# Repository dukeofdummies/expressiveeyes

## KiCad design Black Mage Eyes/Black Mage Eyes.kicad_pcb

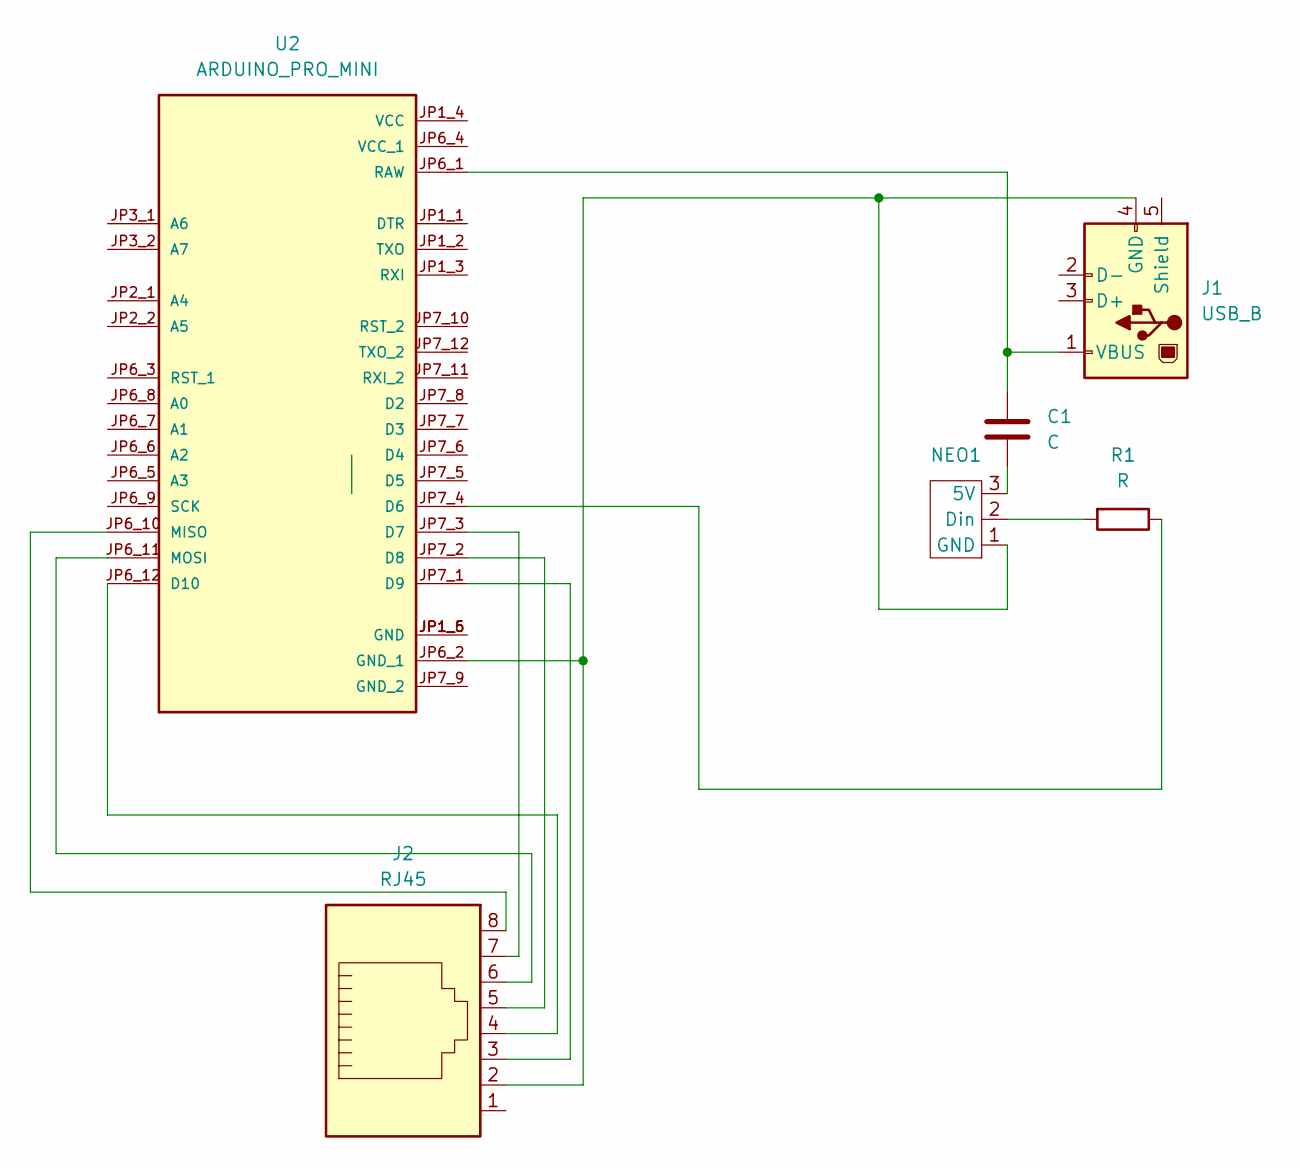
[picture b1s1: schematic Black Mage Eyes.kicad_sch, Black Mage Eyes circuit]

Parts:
C1: C; C_Radial_D8.0mm_H7.0mm_P3.50mm
J1: USB_B; USB_B_Amphenol_MUSB-D511_Vertical_Rugged
J2: RJ45; RJ45_Amphenol_54602-x08_Horizontal
NEO1: PinHeader_1x03_P2.00mm_Vertical
R1: R; R_Axial_DIN0207_L6.3mm_D2.5mm_P7.62mm_Horizontal
U2: ARDUINO_PRO_MINI; MODULE_ARDUINO_PRO_MINI; PARTREV N/A

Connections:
unnamed: J1.4 (GND), J2.2, NEO1.1 (GND), U2.JP6_2 (GND_1)
unnamed: C1.2, J1.1 (VBUS), U2.JP6_1 (RAW)
unnamed: C1.1, NEO1.3 (5V)
unnamed: NEO1.2 (Din), R1.2
unnamed: R1.1, U2.JP7_4 (D6)
unnamed: J2.7, U2.JP7_3 (D7)
unnamed: J2.5, U2.JP7_2 (D8)
unnamed: J2.3, U2.JP7_1 (D9)
unnamed: J2.4, U2.JP6_12 (D10)
unnamed: U2.JP1_5 (GND), U2.JP1_6 (GND)
unnamed: J2.8, U2.JP6_10 (MISO)
unnamed: J2.6, U2.JP6_11 (MOSI)

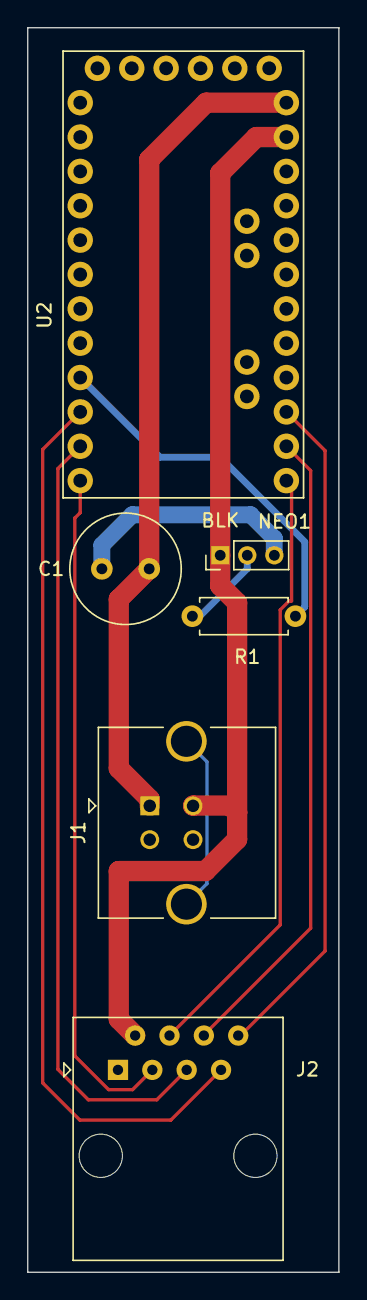
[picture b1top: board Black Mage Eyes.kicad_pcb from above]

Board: 2 copper layers, 23.0 x 92.0 mm, 6 parts (0 on the bottom side), 12 nets.

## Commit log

2023-10-29 Everything I've done so far
    BOM of materials lists the three parts I need to order, the rest are things that I already have in house.
